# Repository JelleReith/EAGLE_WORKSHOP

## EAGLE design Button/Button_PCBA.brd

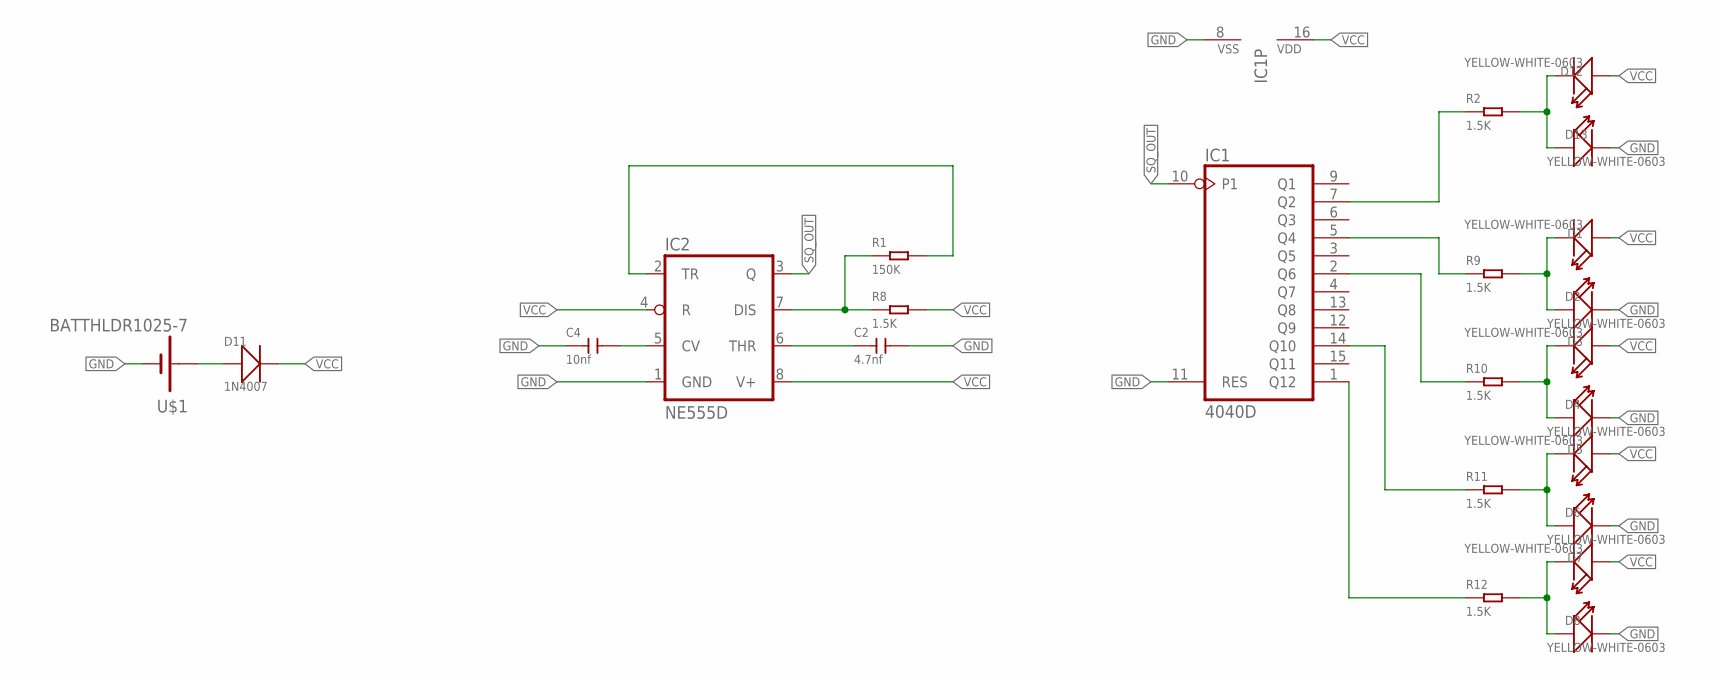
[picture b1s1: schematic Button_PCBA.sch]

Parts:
C2: 4.7nf; C0603
C4: 10nf; C0603
D1, D2, D3, D4, D5, D6, D7, D8, D12, D13: YELLOW-WHITE-0603; LED-0603
D11: 1N4007; DO-214AC
IC1: 4040D; SO16
IC2: NE555D; SO08
R1: 150K; R0603
R2, R8, R9, R10, R11, R12: 1.5K; R0603
U$1: BATTHLDR1025-7

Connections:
+VBAT: D11.1 (+), U$1.POSITIVE (+)
GND: C2.2, C4.1, D2.-, D4.-, D6.-, D8.-, D13.-, IC1.8 (VSS), IC1.11 (RES), IC2.1 (GND), U$1.NEGATIVE (-)
unnamed: C2.1, IC2.6 (THR)
unnamed: IC2.7 (DIS), R1.1, R8.1
unnamed: IC2.2 (TR), R1.2
unnamed: C4.2, IC2.5 (CV)
unnamed: D12.-, D13.+, R2.2
unnamed: IC1.7 (Q2), R2.1
unnamed: D1.-, D2.+, R9.2
unnamed: IC1.5 (Q4), R9.1
unnamed: D3.-, D4.+, R10.2
unnamed: IC1.2 (Q6), R10.1
unnamed: D5.-, D6.+, R11.2
unnamed: IC1.14 (Q10), R11.1
unnamed: D7.-, D8.+, R12.2
unnamed: IC1.1 (Q12), R12.1
SQ_OUT: IC1.10 (P1), IC2.3 (Q)
VCC: D1.+, D3.+, D5.+, D7.+, D11.2 (-), D12.+, IC1.16 (VDD), IC2.4 (R), IC2.8 (V+), R8.2

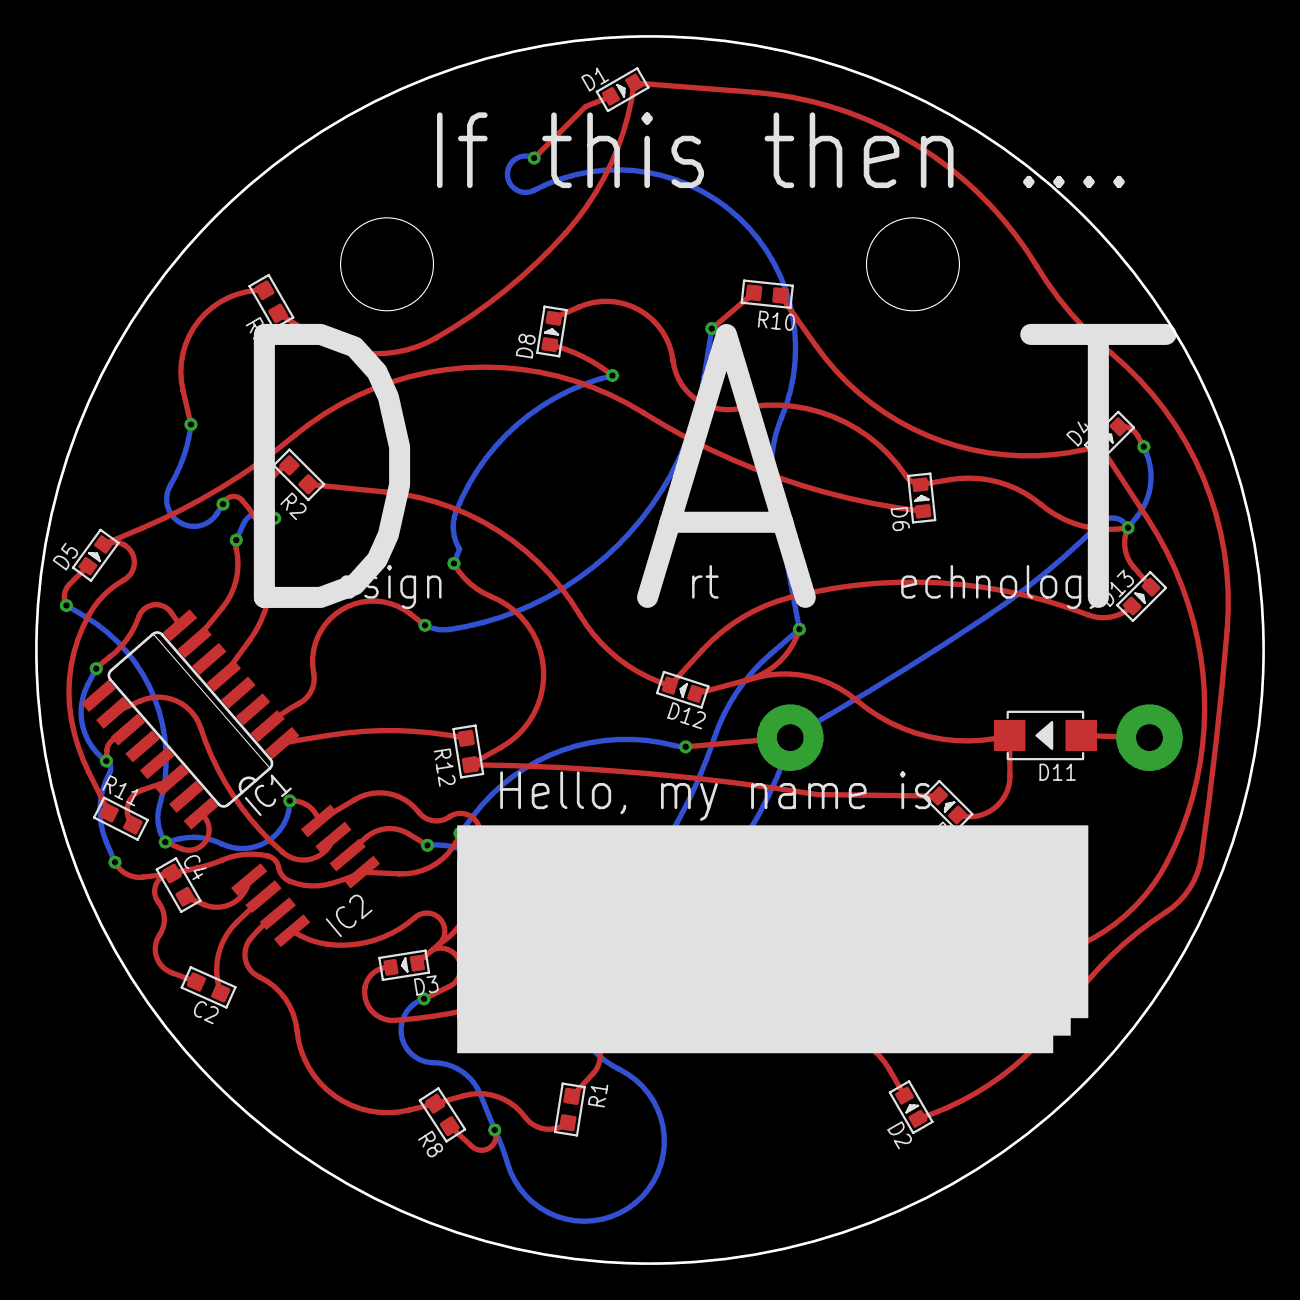
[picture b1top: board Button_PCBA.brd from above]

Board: 2 copper layers, 70.0 x 70.0 mm, 23 parts (1 on the bottom side), 18 nets.

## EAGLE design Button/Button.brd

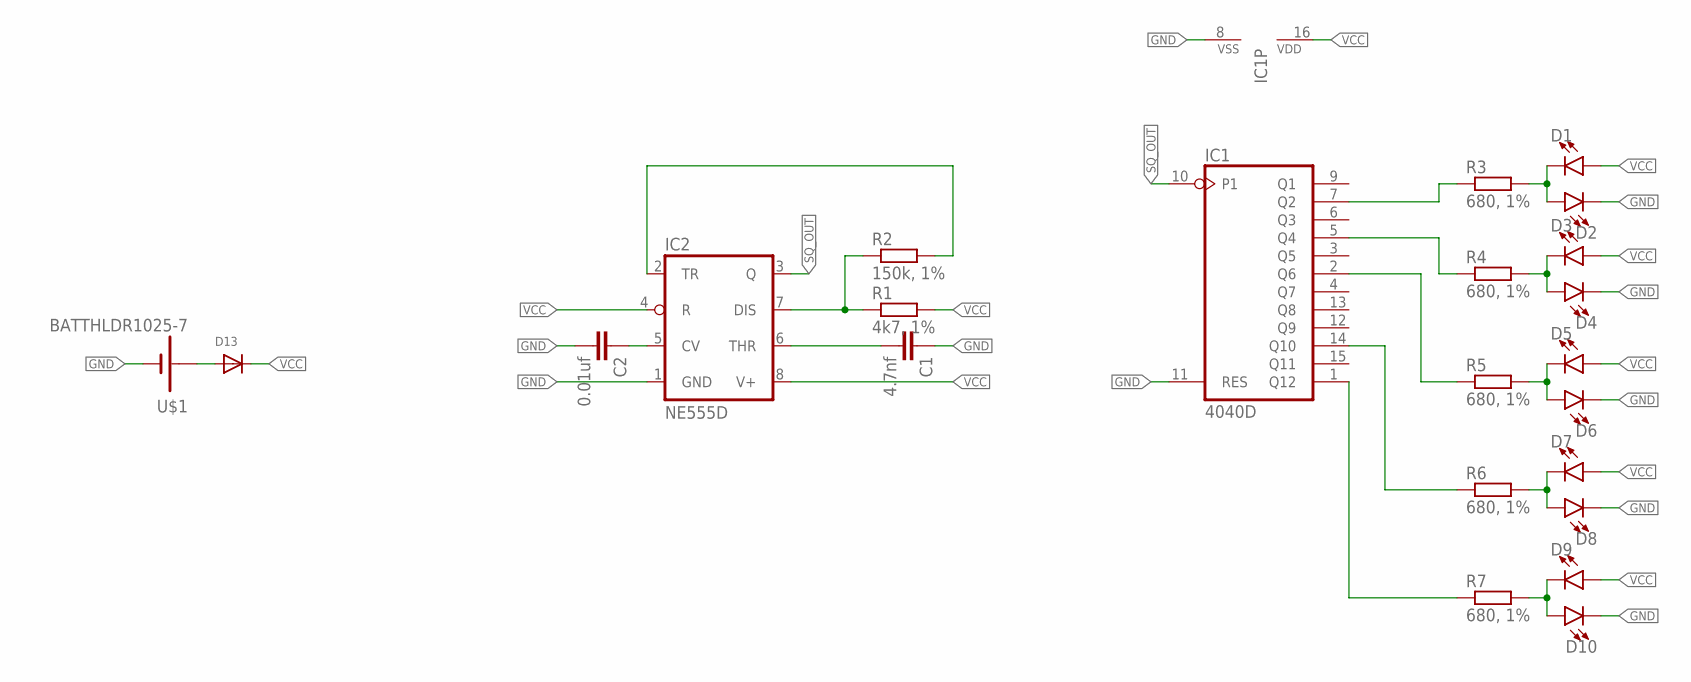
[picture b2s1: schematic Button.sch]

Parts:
C1: 4.7nf; C1206
C2: 0.01uf; C1206
D1, D2, D3, D4, D5, D6, D7, D8, D9, D10: LED1206; LED-1206
D13: DIODESMA; SMADIODE
IC1: 4040D; SO16
IC2: NE555D; SO08
R1: 4k7, 1%; R1206
R2: 150k, 1%; R1206
R3, R4, R5, R6, R7: 680, 1%; R1206
U$1: BATTHLDR1025-7

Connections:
+VBAT: D13.A, U$1.POSITIVE (+)
GND: C1.1, C2.2, D2.C, D4.C, D6.C, D8.C, D10.C, IC1.8 (VSS), IC1.11 (RES), IC2.1 (GND), U$1.NEGATIVE (-)
unnamed: C1.2, IC2.6 (THR)
unnamed: IC2.7 (DIS), R1.1, R2.1
unnamed: IC2.2 (TR), R2.2
unnamed: C2.1, IC2.5 (CV)
unnamed: D1.C, D2.A, R3.2
unnamed: IC1.7 (Q2), R3.1
unnamed: D3.C, D4.A, R4.2
unnamed: IC1.5 (Q4), R4.1
unnamed: D5.C, D6.A, R5.2
unnamed: IC1.2 (Q6), R5.1
unnamed: D7.C, D8.A, R6.2
unnamed: IC1.14 (Q10), R6.1
unnamed: D9.C, D10.A, R7.2
unnamed: IC1.1 (Q12), R7.1
SQ_OUT: IC1.10 (P1), IC2.3 (Q)
VCC: D1.A, D3.A, D5.A, D7.A, D9.A, D13.C, IC1.16 (VDD), IC2.4 (R), IC2.8 (V+), R1.2

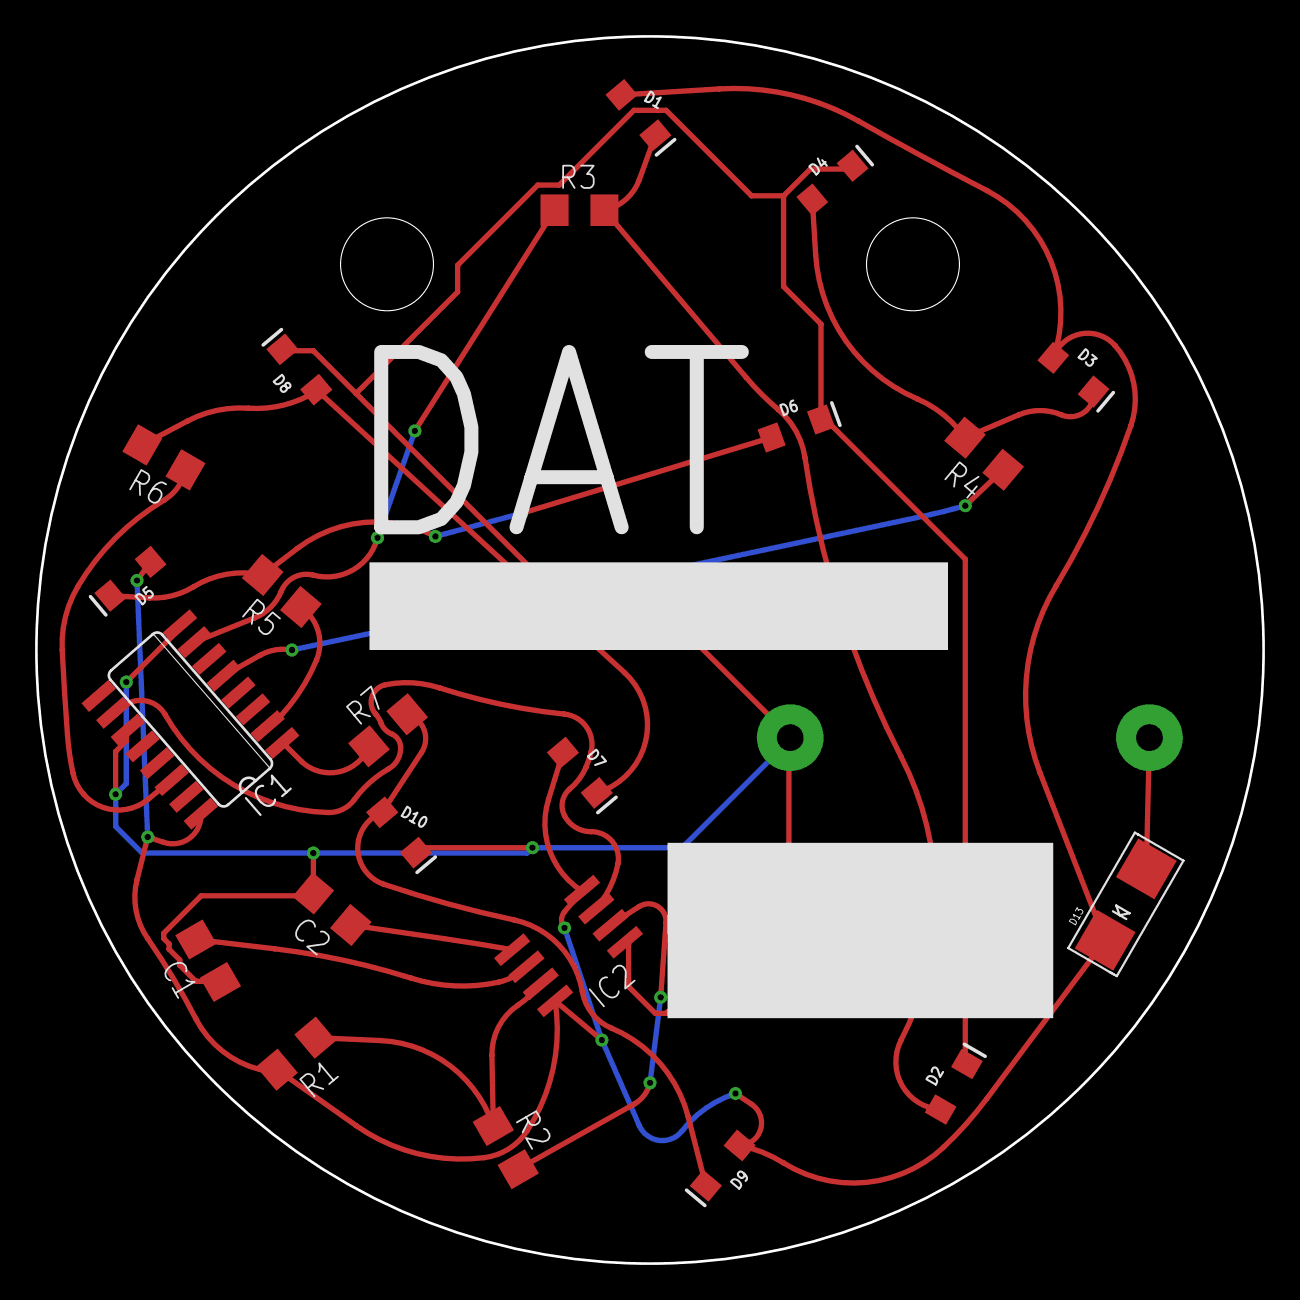
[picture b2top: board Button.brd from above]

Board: 2 copper layers, 70.0 x 70.0 mm, 23 parts (1 on the bottom side), 18 nets.

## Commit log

2021-11-12 initial push
2021-11-19 workshop part 2
2021-11-19 routed
2021-11-22 pcba ready & fusion project

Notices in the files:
parts and their libraries:
SparkFun-LED: Licensing: Creative Commons ShareAlike 4.0 International - https://creativecommons.org/licenses/by-sa/4.0
